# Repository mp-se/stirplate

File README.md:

# PWM controlled stir plate for Beer Brewing

I decided to build my own stir plate and I wanted to use a PWM controlled fan for optimal performance, which requires a microcontroller, since the esp8266 are quite cheap and I happend to have a few lying around this was the natural selection. This also enabled me to measure RPM of the fan and integrate with other things. I'm using this build for my yeast starters with good result and stability. Tests shows that this setup can handle a starter for up to 3 liters (I dont have a bigger glass vessel to test with). The first extension was to add a temperature probe so I can keep track of the wort temperature as well. 

This version can communicate with Blynk server and other software that can handle a standard http post request. With blynk it's also possible to remote control the device and change the power if needed (do override on the potentiometer).

Here is a short video that shows the minimum and maximum speed with a 3 liter starter. The slow speed is around 150 RPM and max speed is 1400 RPM.

[Video of running stir plate](img/speed.mov)

## How does the hardware work ?

I use a potentimeter (5k) to control the speed, this is read via the Analog input (A0) on the ESP (note that this is limited to max 3.3V) so if it's powered by 5V a voltage divider must be used (R1 is used to limit the input to 3.3V). This is mapped towards a PWM signal that is generated by the microcontroller. D5 is used to generate the PWM signal to the FAN and D6 is used to monitor the RPM via interrupt. So the basic design is quite simple. D1 and D2 are used for communicating with the LCD display via I2C.

## Version changes

v1.1.0
* Updated dependences
* Migrated to use my common esp framework
* Updated html pages
* Removed blynk and http post support.

v1.0.2 
* Updated dependences and switched back to 2.6.3
* Fixed minor compiler issues

v1.0.1 
* Forcing wifi into client mode
* Minor update to support ESP8266 SDK v3.0.0

v1.0.0
* First release 

## Installation

You can use VisualStudio Code + Platform IO to handle the device flashing. 

An option could be to use this tool; https://github.com/marcelstoer/nodemcu-pyflasher
Binaries for this is located in the bin folder. 

## Setup

The wifi version will create an WIFI access point at startup called StirPlate (password=password) unless the device has valid wifi settings. A double tap on the reset button will force the device into wifi setup mode. In the portal you can also set the network name of the device (mDNS name). This will have the suffix .local

Once the device is on the wifi network it will have a running webserver that can be used to configure the device. The default name of the device will be __stirplateXXXXX.local__ unless changed in the wifi settings. Use mDNS name or just use the dynamic IP to access the portal. IP adress will be displayed in the serial output from the device during startup. XXXXX is the chip ID and will be 6 characters and uniqe for that device (eg 7a84DC).

### Index

The first page will show information about the operation of the device, RPM, Temperature and Power setting.

### Device

Device page will show current version and device information.

### Configuration

Configuration is used to change the setup and is divided into 4 catagories, Device, Push, Blynk and Hardware.

The settings that can be changed are the following;

* Device name; this is the mDNS (network) name of the device.
* Temperature format; select in which format the temperature value is displayed (Celcius or Farenheigt)
* HTTP Push; URL for posting data (See section below on format details)
* Push Interval; How often should the data be submitted (in seconds)
* Blynk server; Name or IP of the local blynk server. If left empty the blynk cloud will be used.
* Blynk server port; Port for the local blynk server, ignored if blynk cloud is used.
* Blynk token; Token connected to the blynk application, if empty blynk will be disabled.
* Temp sensor adjustment; If you feel that the tempsensor is not showing the correct temperature it's possible to enter a value that will adjust the presented temperature. 
* OTA base URL; OTA base url (use a local webserver since SSL is not used). See section below on more details.

## Build Configuration

I prefer to use Visual Studio Code with the extension PlatformIO which makes it quite easy to make a build.

Development related settings (so I dont have to have a fully working setup)

* LOG_LEVEL=6       Configure Arduino Log (6=Debug, 5=Trace, 4=Notice, 3=Warning, 2=Error, 1=Fatal, 0=Silent)
* SIMULATE_SENSOR   Used to simulate pot readings
* SIMULATE_TEMP     Used to simulate temp readings
* SIMULATE_RPM      Used to simulate pwm readings
* DISPLAY_SELFTEST  Runs some tests on the display at startup

## OTA function

I have added the possibility to do updates via OTA from a local web server over port 80. 

For this to work, place the following files (version.json + firmware.bin) at the location that you pointed out in OTA URL. If the version number in the json file is newer than in the code the update will be done during startup.

Example; OTA URL (don't forget trailing dash), the name of the file should be firmware.bin
```
http://192.168.4.1/firmware/stirplate/
```

Contents version.json
```
{ "project":"stirplate", "version":"0.3.0" }
```

## Materials

In order to build this project you will need the following;

Schema and PCB is avaialble under the cad folder, these are designed in Eagle (Free version) and can be downloaded from Autodesk. Note! That these are not yet tested and verified. For my build I used a standard breadbord. 

* U1 - Microcontroller ESP8266 (WEMOS D1 Mini)
* IC1- DS28B20 (Temperature probe)
* IC2- Power regulator 12V -> 5V (I used LD1085V50)
* R1 - Resistor 3.3k 
* R2 - Potentiometer 5k
* R3 - Resistor 3.3k
* R4 - Resistor 4.7k
* C1 - 10uF
* C2 - 10uF
* 2 x 4PIN connectors for display and fan.
* I2C compatible display - I used a 2x16 LCD
* PCB for mounting components
* FAN with PWM (4-pin) - I used Noctua NF-B9 rexux 1600 
* Box large enough to hold the FAN and electronics
* Power supply 12VAC - 1A
* 2 neodym magnets (glued to fan)

A schematics that I used can be found in the cad directory. [Electronic schema](cad/stirplate.pdf)

There is also a PCB example that has not yet been verified.

On my build I cut of the wings to the FAN, this increased the maximum RPM from 1800 -> 2700. I glued the fan to the box lid with some spacers to make sure there is enough distance for the fan to spin. 

Feel free to use the code and modify your own build. Contributions and ideas for improvements are welcomed.

Happy building. 
/Magnus

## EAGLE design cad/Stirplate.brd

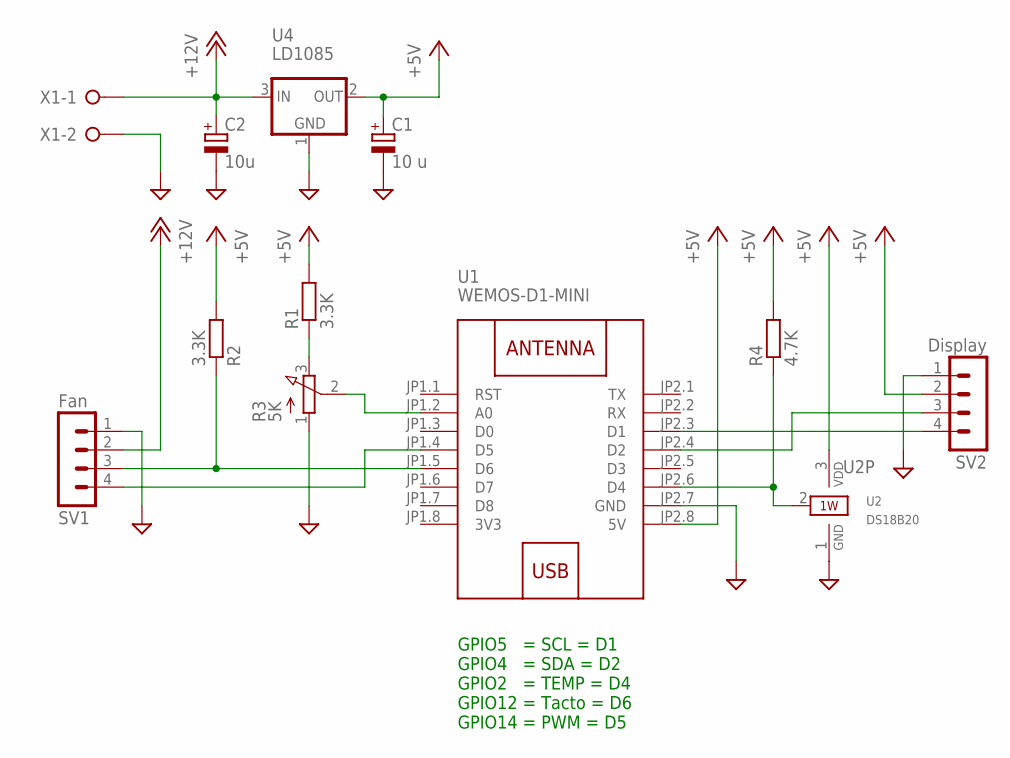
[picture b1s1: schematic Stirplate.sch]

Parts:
C1: 10 u; E2,5-5
C2: 10u; E2,5-5
R1, R2: 3.3K; 0207/10
R3: 5K; 3RP/1610N
R4: 4.7K; 0207/10
SV1: Fan; MA04-1
SV2: Display; MA04-1
U1: WEMOS-D1-MINI
U2: DS18B20; TO92-
U4: PMX42_LD1086VXX-H; PMX42_TO220-NH
X1: W237-02P; W237-132

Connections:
1W: R4.1, U1.JP2.6 (D4), U2.2 (1W)
3V3: U1.JP1.8 (3V3)
+5V: C1.+, R1.2, R2.2, R4.2, SV2.2, U1.JP2.8 (5V), U2.3 (VDD), U4.2 (OUT)
+12V: C2.+, SV1.2, U4.3 (IN), X1.1
GND: C1.-, C2.-, R3.1 (A), SV1.1, SV2.1, U1.JP2.7 (GND), U2.1 (GND), U4.1 (GND), X1.2
unnamed: R3.2 (S), U1.JP1.2 (A0)
unnamed: R1.1, R3.3 (E)
unnamed: R2.1, SV1.3, U1.JP1.5 (D6)
unnamed: SV1.4, U1.JP1.4 (D5)
unnamed: SV2.3, U1.JP2.4 (D2)
unnamed: SV2.4, U1.JP2.3 (D1)

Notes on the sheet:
GPIO5 = SCL = D1 GPIO4 = SDA = D2 GPIO2 = TEMP = D4 GPIO12 = Tacto = D6 GPIO14 = PWM = D5

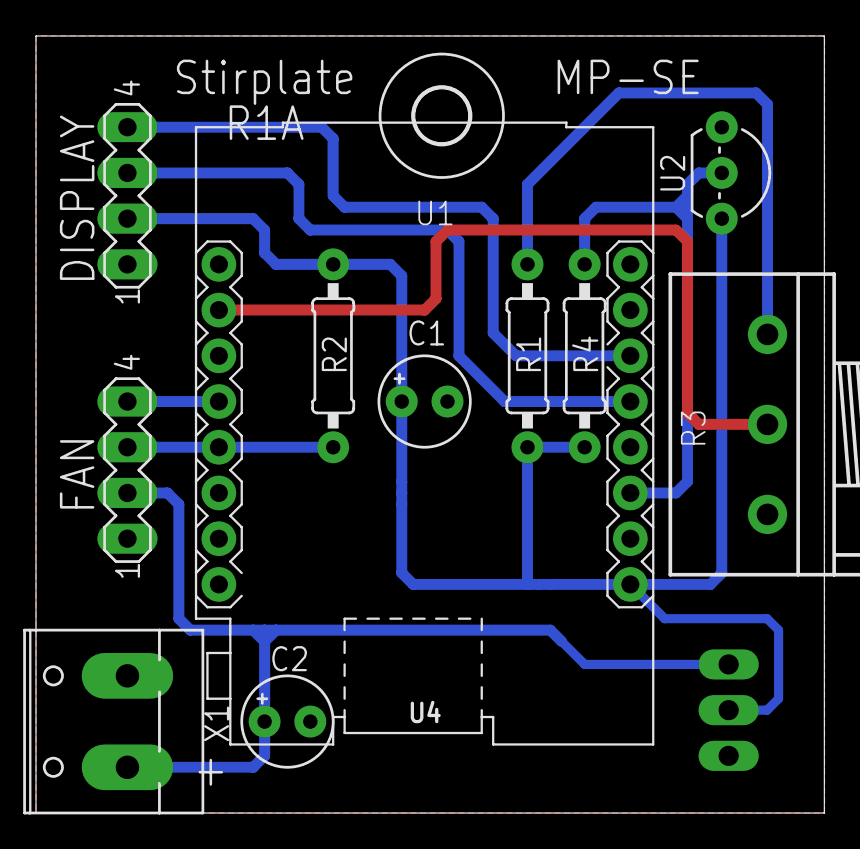
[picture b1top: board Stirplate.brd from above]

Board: 2 copper layers, 43.8 x 43.2 mm, 13 parts (0 on the bottom side), 10 nets.

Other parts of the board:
U$3: 3,0

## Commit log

2021-01-26 First release
2021-01-26 Added files to gitignore
2021-01-27 Refactoring
2021-01-29 Added OTA support
2021-01-29 Minor refactoring
2021-01-29 Added option to disable wifi in build
2021-01-29 Added option to remove OTA
2021-01-29 Bump version 0.3.1
2021-01-30 Documentation + Blynk port in secrets
2021-01-31 Updated doc + prepare for temp sensor
2021-02-01 WifiManager and config added
2021-02-02 Refactoring + wifimgr
2021-02-02 Missed clearing one char on text output
2021-02-02 Added tempsensor code
2021-02-02 Updated temp sensor code and blynk
2021-02-04 Draft PCB with Eagle
2021-02-07 Refactor
2021-02-09 Moved out project specifc settings
2021-02-14 Fixed minor bugs
2021-02-14 Version for testing temperature support
2021-02-15 Added double tap into wifi mgr
2021-02-15 Up to version 0.4.2 for testing
2021-02-15 Modified rpm reading to get more stable #
2021-02-15 Updated to v0.5
2021-02-24 Added get/set methods for config class
2021-02-24 Added http push target
2021-02-24 Added simple api for config
2021-02-24 Updated docs
2021-02-24 Remove temp files from git
2021-02-24 Test cases for api's
2021-02-24 Testing v1.5.1
2021-02-25 Added support for blynk cloud
2021-02-25 Added id check to reset/wifi calls
2021-02-25 Updated docs.
2021-02-25 Updated to v0.6
2021-03-09 Refactor loop to improve response of pot
2021-03-18 Changed DynamicJson + LittleFS.end
2021-03-25 Version for testing
2021-03-25 Test version 0.6.4
2021-03-28 Changed wifimanager library
2021-03-29 Refactor config class
2021-03-29 Updated documentation
2021-03-29 Test build
2021-03-30 Build new testversion
2021-04-01 Updated and tested wifimanager
2021-04-01 Added binaries
2021-04-10 Updated documentation for v1.0
2021-05-30 Updated with latest arduinolog
2022-01-02 Updated library dependecies
2022-01-02 Bumped version to 1.0.2
2022-01-02 Testing github actions for dev
2022-01-02 Corrected extension
2022-01-02 Changed name of include
2022-01-02 Change to unix style path
2022-06-14 Added precommit config
2022-06-14 Updated html to bs5
2022-06-14 Adopted to my espfwk
2022-06-14 New test response
2022-06-14 Updated deps
2022-06-15 Fixed rpm code
2022-06-15 Fix html
2022-06-15 Test version
2022-06-15 Upd build action
2022-06-15 Linux build fix
2022-06-15 GitHub Action Build
2022-06-15 Remove old bin
2022-06-15 Upd readme
2023-03-20 Updated for espfwk 0.6

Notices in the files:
parts and their libraries:
diy-modules: Released under the Creative Commons Attribution 4.0 International License: http://creativecommons.org/licenses/by/4.0
